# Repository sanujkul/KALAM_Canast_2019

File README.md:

# KALAM_Canast_2019    
These codes/files were written/developed for the Cansat competition 2019, USA.    

This folder have two types of files:  
1. Codes (.c, .c++, .ino)    
2. PCB designs    
  
Cansat 2019 was divided ino two parts: A payload and a container. Cansat is launched to the height of 750m and at the height of 450m, during descent journey,container would release the payload which will descent via auto-gyro mechanism.    
Cansat has to perform telemetry throughout its journey.   
  
Files descriptions:  
a. TeensyPayloadCodes : Have the Cansat's payload codes.   
b. Container_Final : Have the Cansat's container codes.    
c. Camera Stabilization Codes: Payload was divided into 2 subparts, minor subpart was camra stabilization system and these are codes for stabilizing the camera to shoot in a particular direction.   
d. Camera_Stabilisation_Tests: Codes written for testing Camera stabilization system.  
e. Bluetooth Tests: Camera stabilization setup used to communicate to main microcontroller (Teensy) via bluetooth and these are test codes for that.   
f. SumiranPCB: Contains PCB designs (Eagle Cad files) for the cansat.  
g. Packets: This is a class developed to use telemetry packet as an object to ease or work in organising the codeflow.

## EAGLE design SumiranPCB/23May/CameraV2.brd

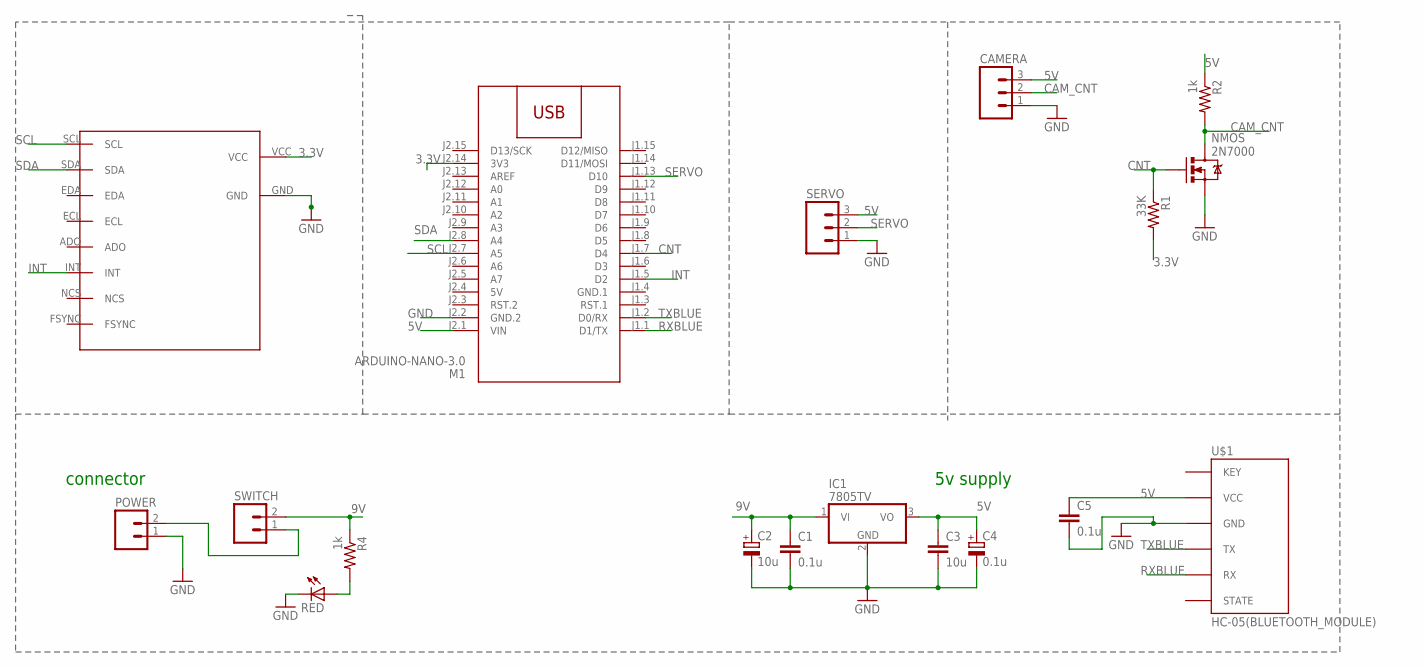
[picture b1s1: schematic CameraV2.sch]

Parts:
C1, C5: 0.1u; C025-025X050
C2: 10u; E2,5-6
C3: 10u; C025-025X050
C4: 0.1u; E2,5-6
CAMERA: CON-AMP-QUICK_M03; CON-AMP-QUICK_03P
IC1: 7805TV; TO220V
M1: ARDUINO-NANO-3.0
POWER: CEDT_JANUARY_2015_V5_M02; CEDT_JANUARY_2015_V5_02P
Q1: SPARKFUN-DISCRETESEMI_MOSFET-NCHANNEL2N7000; SPARKFUN-DISCRETESEMI_TO-92
R1: 33K; 0204/7
R2, R4: 1k; 0204/7
RED: red; LED3MM
SERVO: CON-AMP-QUICK_M03; CON-AMP-QUICK_03P
SWITCH: M02; 02P
U$1: HC-05(BLUETOOTH_MODULE); HC-05
U$2: MPU9250

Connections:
3.3V: M1.J2.14 (3V3), R1.2, U$2.VCC
5V: C3.1, C4.+, C5.1, CAMERA.3, IC1.3 (VO), M1.J2.1 (VIN), M1.J2.4 (5V), R2.1, SERVO.3, U$1.VCC
9V: C1.1, C2.+, IC1.1 (VI), R4.1, SWITCH.2
CAM_CNT: CAMERA.2, Q1.3 (D), R2.2
CNT: M1.J1.7 (D4), Q1.2 (G), R1.1
GND: C1.2, C2.-, C3.2, C4.-, C5.2, CAMERA.1, IC1.2 (GND), M1.J2.2 (GND.2), POWER.1, Q1.1 (S), RED.K (C), SERVO.1, U$1.GND, U$2.GND
GND.1: M1.J1.4 (GND.1)
INT: M1.J1.5 (D2), U$2.INT
unnamed: POWER.2, SWITCH.1
unnamed: R4.2, RED.A
RXBLUE: M1.J1.1 (D1/TX), U$1.RX
SCL: M1.J2.7 (A5), U$2.SCL
SDA: M1.J2.8 (A4), U$2.SDA
SERVO: M1.J1.13 (D10), SERVO.2
TXBLUE: M1.J1.2 (D0/RX), U$1.TX

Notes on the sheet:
connector
5v supply

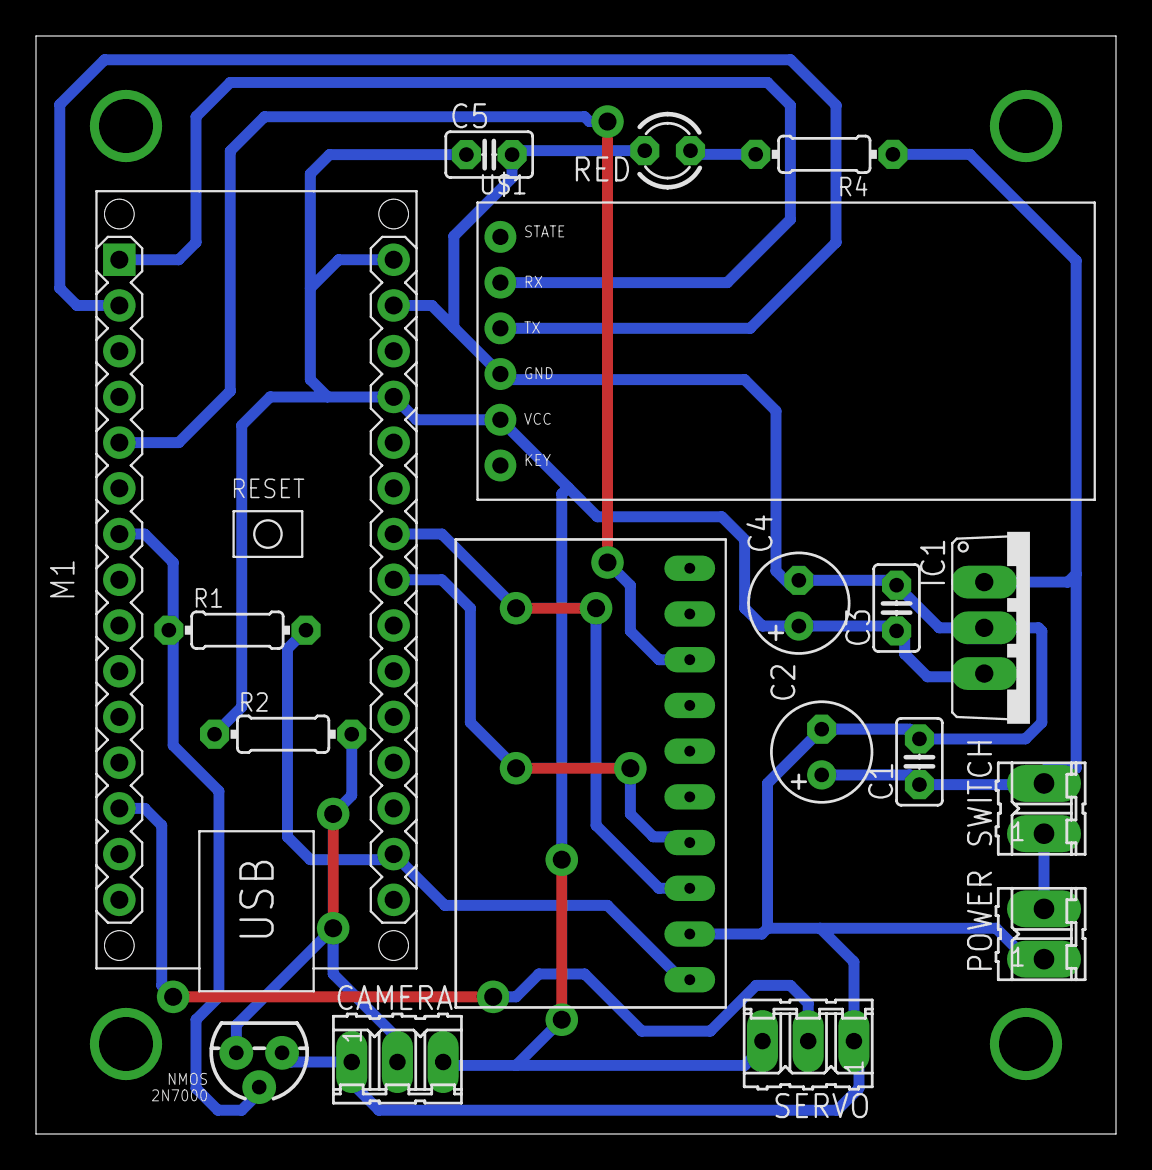
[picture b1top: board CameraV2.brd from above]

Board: 2 copper layers, 60.0 x 61.0 mm, 18 parts (0 on the bottom side), 14 nets.

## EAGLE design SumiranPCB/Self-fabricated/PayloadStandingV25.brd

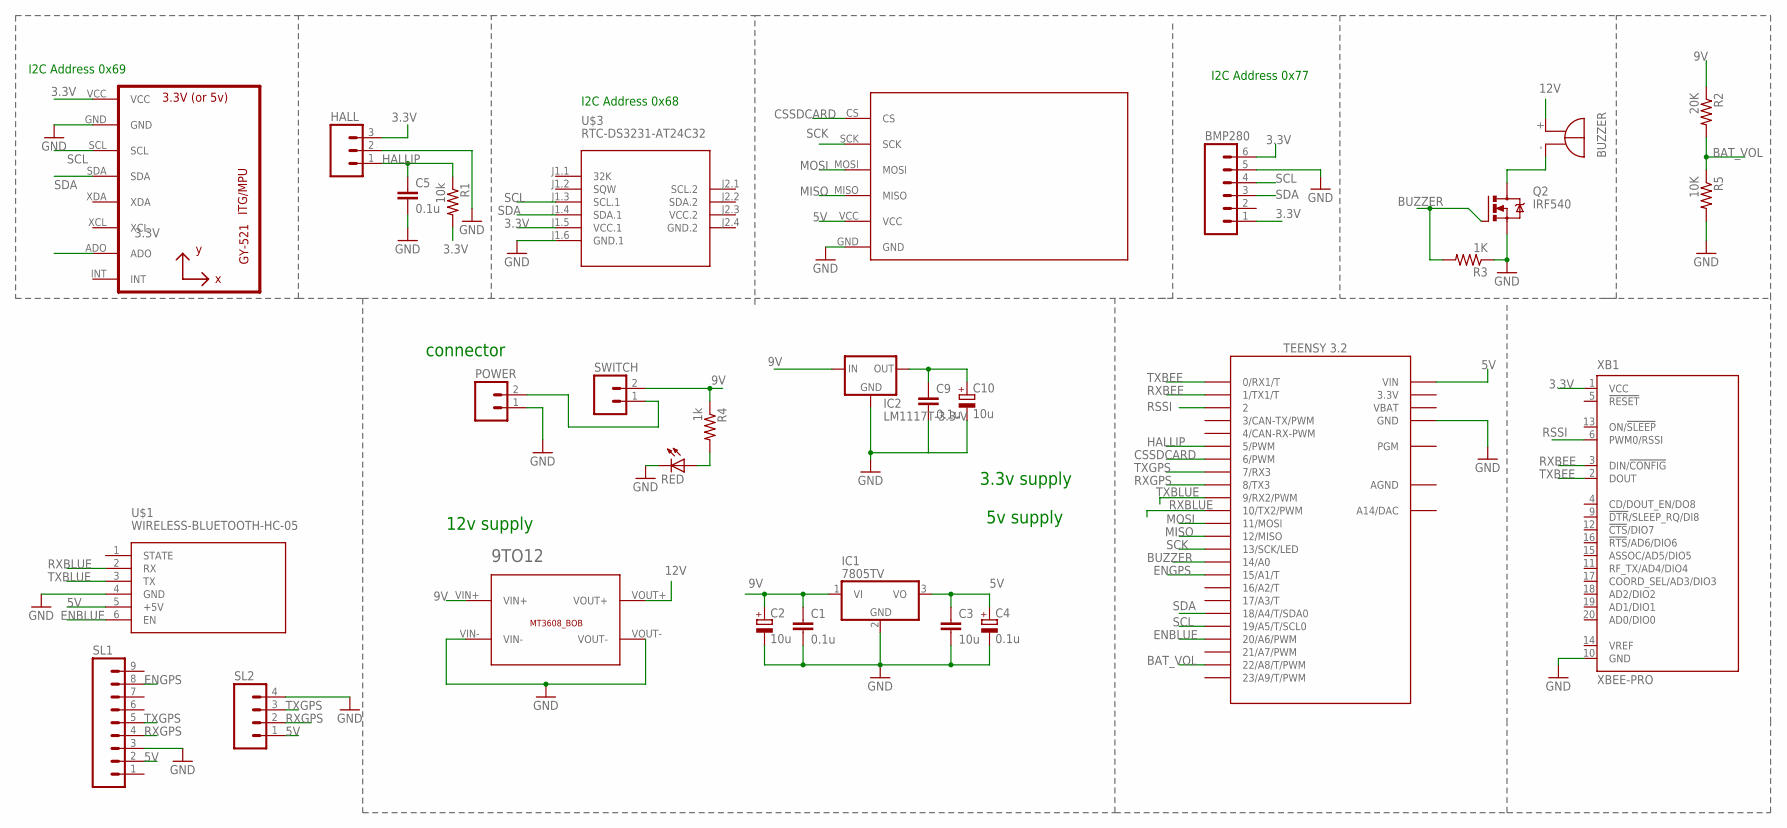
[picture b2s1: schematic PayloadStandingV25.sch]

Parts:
9TO12: BREAKOUTS_MT3608_BOB
BMP280: M06; 06P
C1, C5, C9: 0.1u; C025-025X050
C2, C10: 10u; E2,5-6
C3: 10u; C025-025X050
C4: 0.1u; E2,5-6
HALL: M03; 03P
IC1: 7805TV; TO220V
IC2: LM1117T-3.3-V; TO220V
POWER: CEDT_JANUARY_2015_V5_M02; CEDT_JANUARY_2015_V5_02P
Q2: IRF540; TO220BV
R1: 10k; 0204/7
R2: 20K; 0204/7
R3: 1K; 0204/7
R4: 1k; 0204/7
R5: 10K; 0204/7
RED: red; LED3MM
SG1: BUZZER_EB2209A
SL1: M09; 09P
SL2: CON-AMP-QUICK_M04; CON-AMP-QUICK_04P
SWITCH: M02; 02P
U1: GY-521MPU6050; GY-521
U$1: WIRELESS-BLUETOOTH-HC-05
U$2: TEENSY_3.1-3.2_OUTER_ROW; TEENSY_3.0-3.2&LC_OUTER_ROW
U$3: RTC-DS3231-AT24C32
U$5: SDCARD; M0SDCARDMODULE
XB1: XBEE-PRO

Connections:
3.3V: BMP280.1, BMP280.6, C9.1, C10.+, HALL.3, IC2.2 (OUT), R1.2, U1.ADO, U1.VCC, U$2.3.3V, U$2.3.3V1 (3.3V), U$3.J1.5 (VCC.1), XB1.1 (VCC)
5V: C3.1, C4.+, IC1.3 (VO), SL1.2, SL2.1, U$1.5 (+5V), U$2.VIN, U$5.VCC
9V: 9TO12.VIN+, C1.1, C2.+, IC1.1 (VI), IC2.3 (IN), R2.1, R4.1, SWITCH.2
12V: 9TO12.VOUT+, SG1.+
AGND: U$2.AGND
BAT_VOL: R2.2, R5.1, U$2.22/A8 (22/A8/T/PWM)
BUZZER: Q2.G, R3.2, U$2.14/A0
CSSDCARD: U$2.6 (6/PWM), U$5.CS
ENBLUE: U$1.6 (EN), U$2.20/A6 (20/A6/PWM)
ENGPS: SL1.8, U$2.15/A1 (15/A1/T)
GND: 9TO12.VIN-, 9TO12.VOUT-, BMP280.5, C1.2, C2.-, C3.2, C4.-, C5.2, C9.2, C10.-, HALL.2, IC1.2 (GND), IC2.1 (GND), POWER.1, Q2.S, R3.1, R5.2, RED.K (C), SL1.3, SL2.4, U1.GND, U$1.4 (GND), U$2.GND, U$2.GND1 (GND), U$3.J1.6 (GND.1), U$5.GND, XB1.10 (GND)
GND.2: U$3.J2.4 (GND.2)
HALLIP: C5.1, HALL.1, R1.1, U$2.5 (5/PWM)
MISO: U$2.12 (12/MISO), U$5.MISO
MOSI: U$2.11 (11/MOSI), U$5.MOSI
unnamed: POWER.2, SWITCH.1
unnamed: R4.2, RED.A
unnamed: Q2.D, SG1.-
RSSI: U$2.2, XB1.6 (PWM0/RSSI)
RXBEE: U$2.1 (1/TX1/T), XB1.3 (DIN/!CONFIG)
RXBLUE: U$1.2 (RX), U$2.10 (10/TX2/PWM)
RXGPS: SL1.4, SL2.2, U$2.8 (8/TX3)
SCK: U$2.13 (13/SCK/LED), U$5.SCK
SCL: BMP280.4, U1.SCL, U$2.19/A5 (19/A5/T/SCL0), U$3.J1.3 (SCL.1)
SDA: BMP280.3, U1.SDA, U$2.18/A4 (18/A4/T/SDA0), U$3.J1.4 (SDA.1)
TXBEE: U$2.0 (0/RX1/T), XB1.2 (DOUT)
TXBLUE: U$1.3 (TX), U$2.9 (9/RX2/PWM)
TXGPS: SL1.5, SL2.3, U$2.7 (7/RX3)
VBAT: U$2.VBAT
VCC.2: U$3.J2.3 (VCC.2)

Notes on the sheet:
connector
3.3v supply
5v supply
12v supply
I2C Address 0x77
I2C Address 0x68
I2C Address 0x69

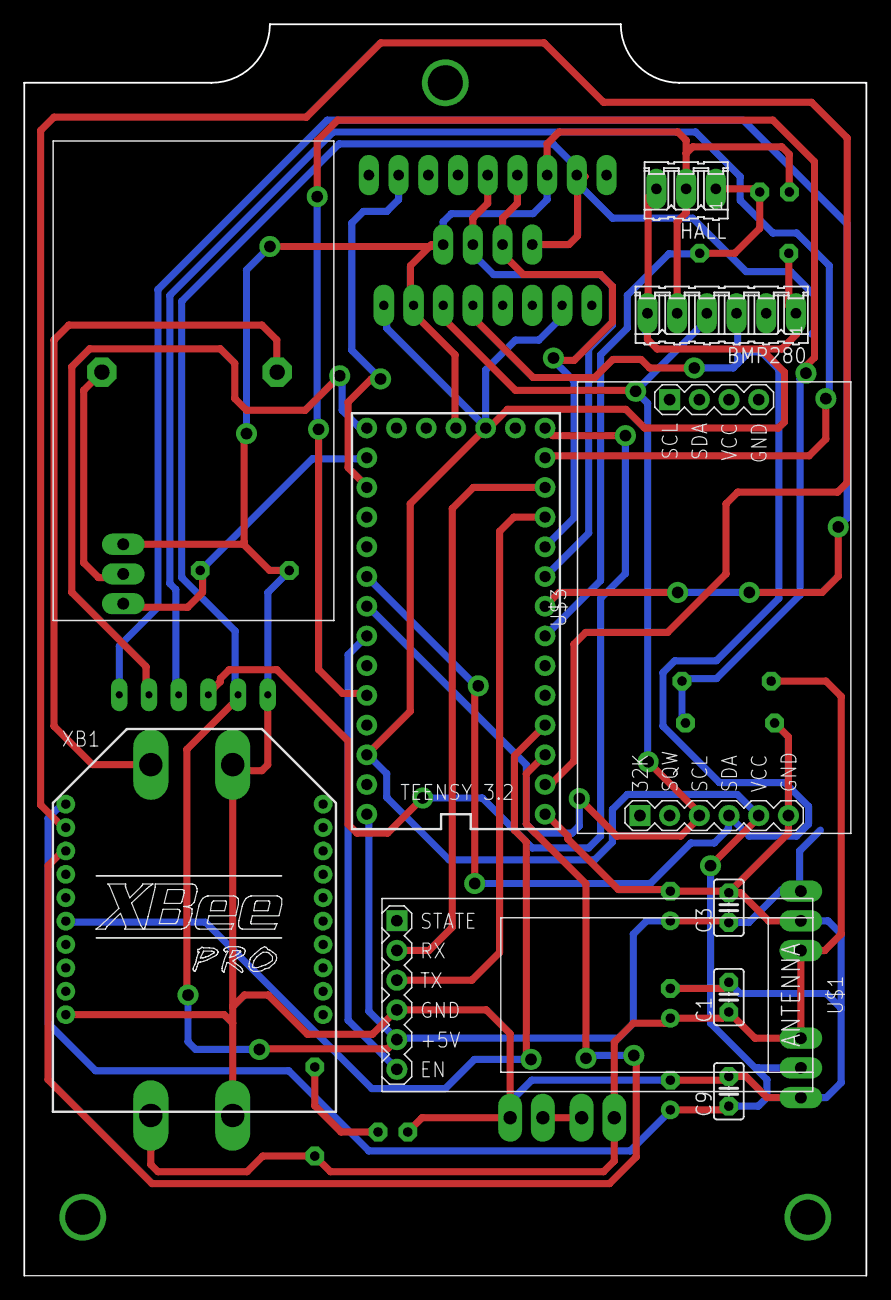
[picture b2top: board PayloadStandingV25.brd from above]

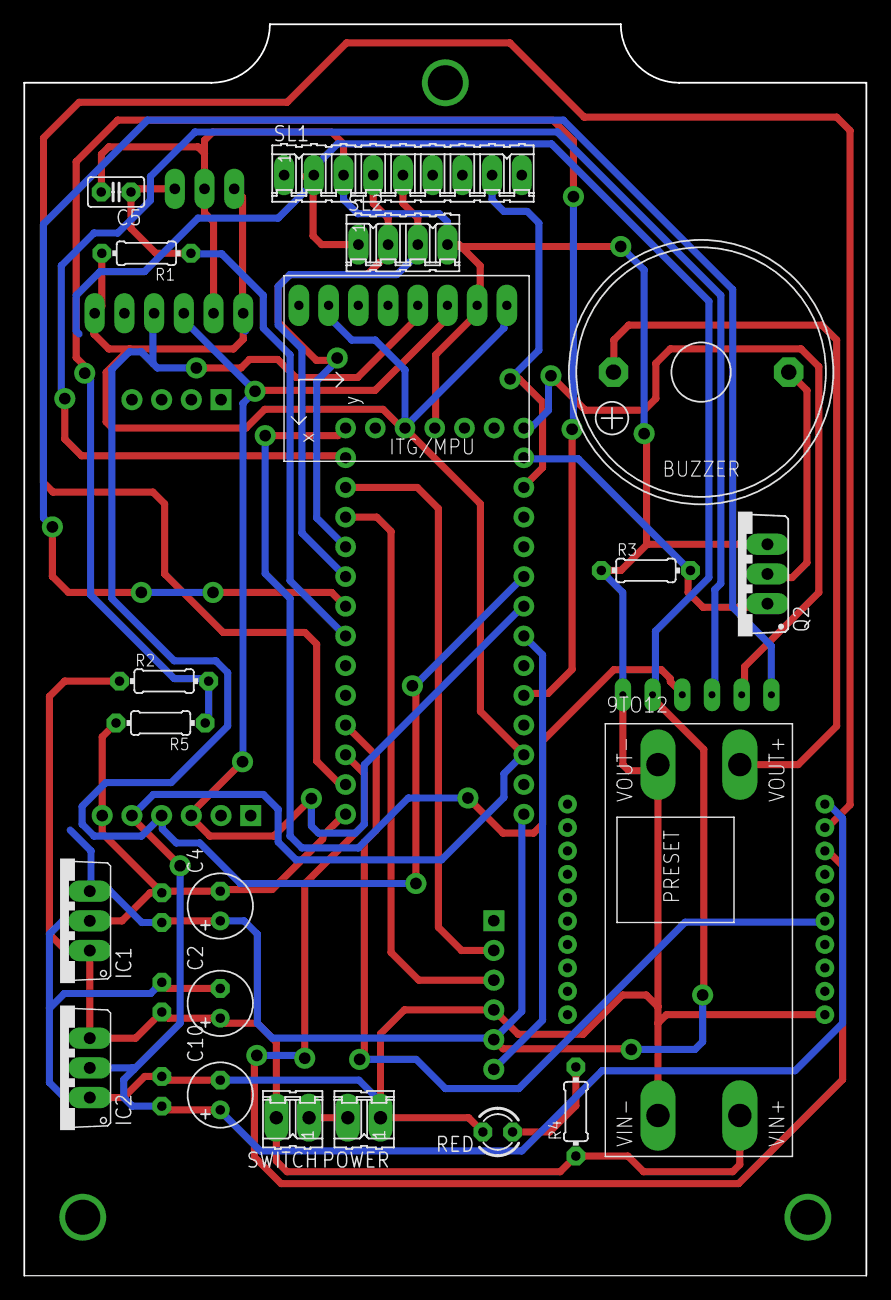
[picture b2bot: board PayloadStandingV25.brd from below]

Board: 2 copper layers, 72.0 x 107.0 mm, 30 parts (20 on the bottom side), 26 nets.

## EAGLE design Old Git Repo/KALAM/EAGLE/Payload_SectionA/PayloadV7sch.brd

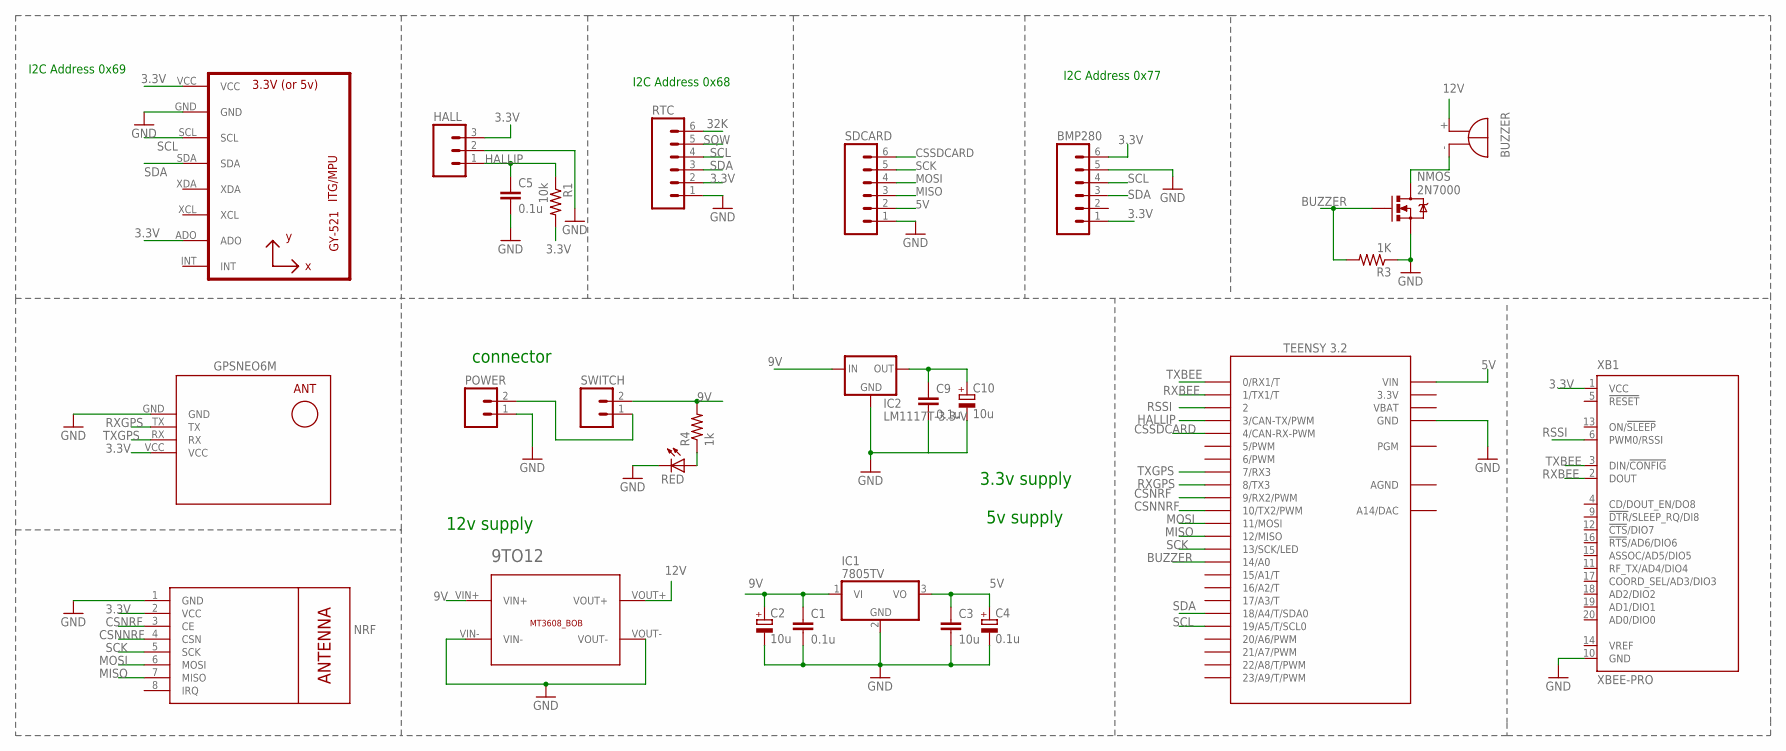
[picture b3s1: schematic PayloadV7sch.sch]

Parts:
9TO12: BREAKOUTS_MT3608_BOB
BMP280: M06; 06P
C1, C5, C9: 0.1u; C025-025X050
C2, C10: 10u; E2,5-6
C3: 10u; C025-025X050
C4: 0.1u; E2,5-6
HALL: M03; 03P
IC1: 7805TV; TO220V
IC2: LM1117T-3.3-V; TO220V
M1: WIRELESS-NRF24L01
POWER: CEDT_JANUARY_2015_V5_M02; CEDT_JANUARY_2015_V5_02P
Q1: SPARKFUN-DISCRETESEMI_MOSFET-NCHANNEL2N7000; SPARKFUN-DISCRETESEMI_TO-92
R1: 10k; 0204/7
R3: 1K; 0204/7
R4: 1k; 0204/7
RED: red; LED3MM
RTC: M06; 06P
SDCARD: M06; 06P
SG1: BUZZER_EB2209A
SWITCH: CEDT_JANUARY_2015_V5_M02; CEDT_JANUARY_2015_V5_02P
U1: GY-521MPU6050; GY-521
U$2: TEENSY_3.1-3.2_OUTER_ROW; TEENSY_3.0-3.2&LC_OUTER_ROW
U$3: GPS-RECEIVER-NEO6M
XB1: XBEE-PRO

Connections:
3.3V: BMP280.1, BMP280.6, C9.1, C10.+, HALL.3, IC2.2 (OUT), M1.2 (VCC), R1.2, RTC.2, U1.ADO, U1.VCC, U$2.3.3V, U$2.3.3V1 (3.3V), U$3.VCC, XB1.1 (VCC)
5V: C3.1, C4.+, IC1.3 (VO), SDCARD.2, U$2.VIN
9V: 9TO12.VIN+, C1.1, C2.+, IC1.1 (VI), IC2.3 (IN), R4.2
12V: 9TO12.VOUT+, SG1.+
32K: RTC.6
AGND: U$2.AGND
BUZZER: Q1.2 (G), R3.2, U$2.14/A0
CSNNRF: M1.4 (CSN), U$2.10 (10/TX2/PWM)
CSNRF: M1.3 (CE), U$2.9 (9/RX2/PWM)
CSSDCARD: SDCARD.6, U$2.4 (4/CAN-RX-PWM)
GND: 9TO12.VIN-, 9TO12.VOUT-, BMP280.5, C1.2, C2.-, C3.2, C4.-, C5.2, C9.2, C10.-, HALL.2, IC1.2 (GND), IC2.1 (GND), M1.1 (GND), POWER.1, Q1.1 (S), R3.1, RED.K (C), RTC.1, SDCARD.1, U1.GND, U$2.GND, U$2.GND1 (GND), U$3.GND, XB1.10 (GND)
HALLIP: C5.1, HALL.1, R1.1, U$2.3 (3/CAN-TX/PWM)
MISO: M1.7 (MISO), SDCARD.3, U$2.12 (12/MISO)
MOSI: M1.6 (MOSI), SDCARD.4, U$2.11 (11/MOSI)
unnamed: R4.1, RED.A
unnamed: Q1.3 (D), SG1.-
RSSI: U$2.2, XB1.6 (PWM0/RSSI)
RXBEE: U$2.1 (1/TX1/T), XB1.2 (DOUT)
RXGPS: U$2.8 (8/TX3), U$3.TX
SCK: M1.5 (SCK), SDCARD.5, U$2.13 (13/SCK/LED)
SCL: BMP280.4, RTC.4, U1.SCL, U$2.19/A5 (19/A5/T/SCL0)
SDA: BMP280.3, RTC.3, U1.SDA, U$2.18/A4 (18/A4/T/SDA0)
SQW: RTC.5
TXBEE: U$2.0 (0/RX1/T), XB1.3 (DIN/!CONFIG)
TXGPS: U$2.7 (7/RX3), U$3.RX
VBAT: U$2.VBAT

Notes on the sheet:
connector
3.3v supply
5v supply
12v supply
I2C Address 0x77
I2C Address 0x68
I2C Address 0x69

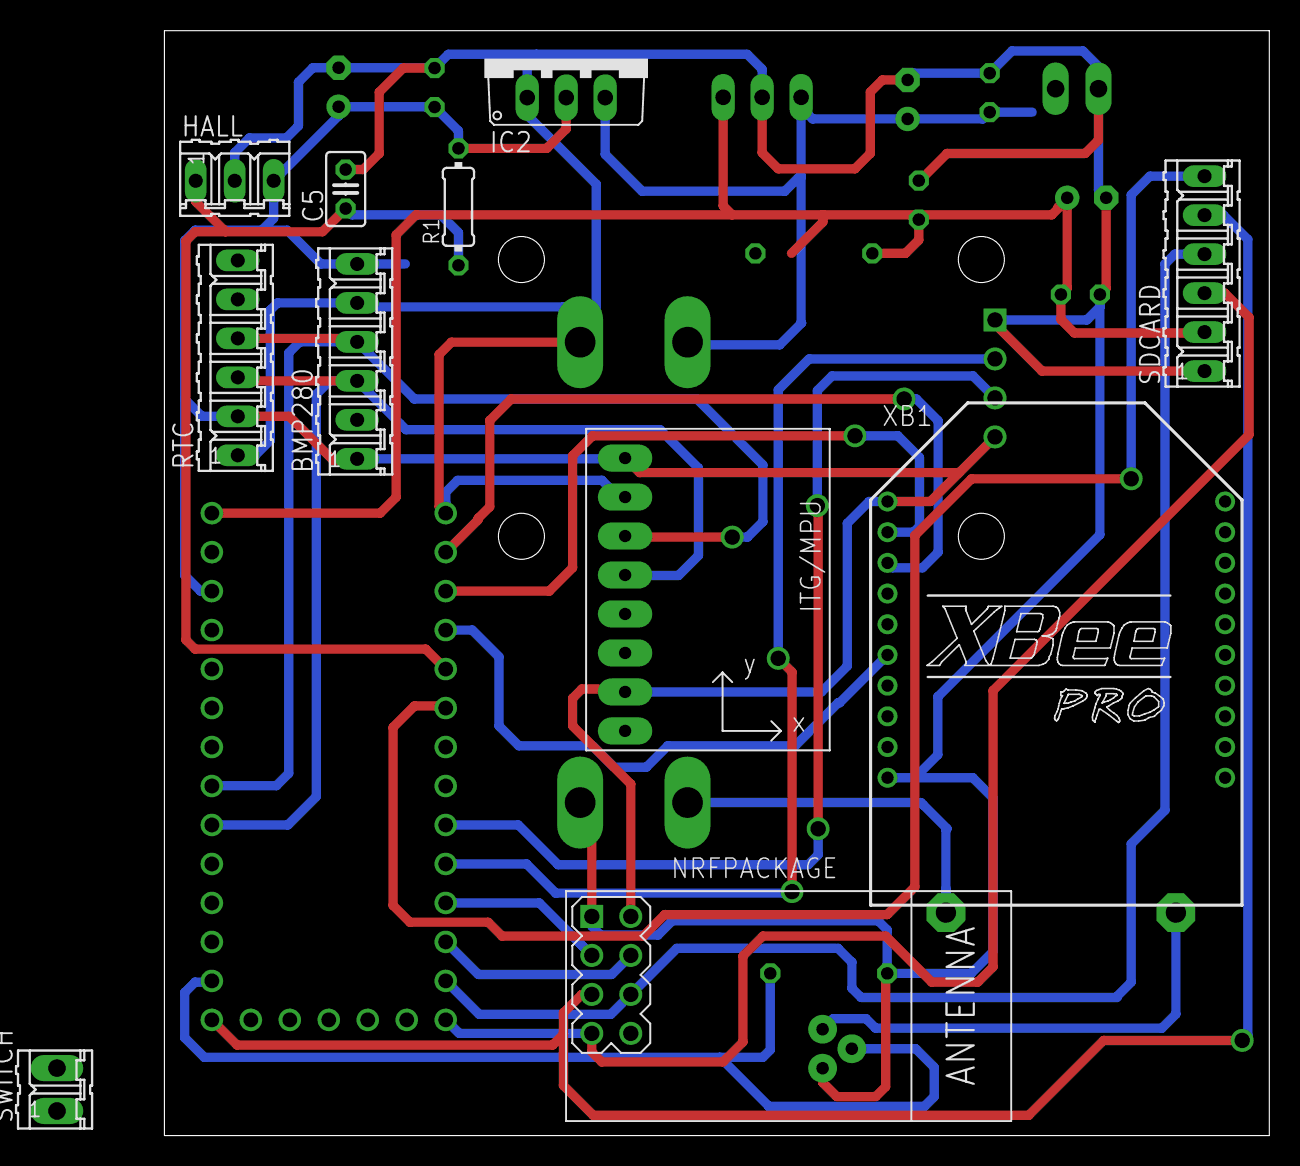
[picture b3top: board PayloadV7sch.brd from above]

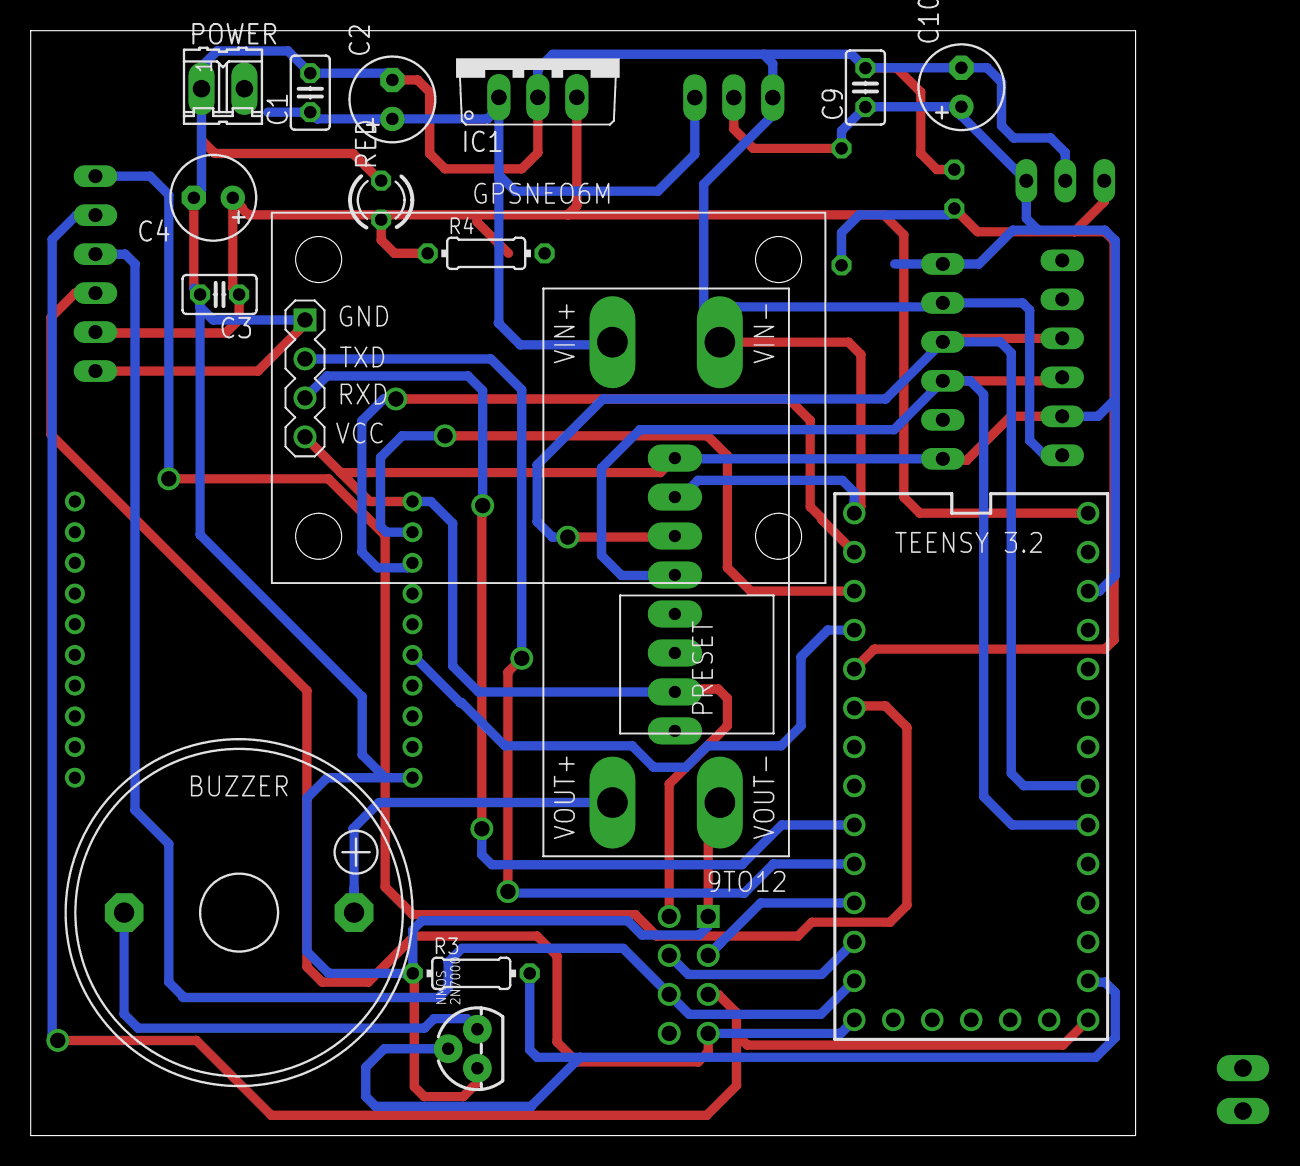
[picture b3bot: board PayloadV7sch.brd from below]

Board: 2 copper layers, 72.0 x 72.0 mm, 27 parts (16 on the bottom side), 22 nets.

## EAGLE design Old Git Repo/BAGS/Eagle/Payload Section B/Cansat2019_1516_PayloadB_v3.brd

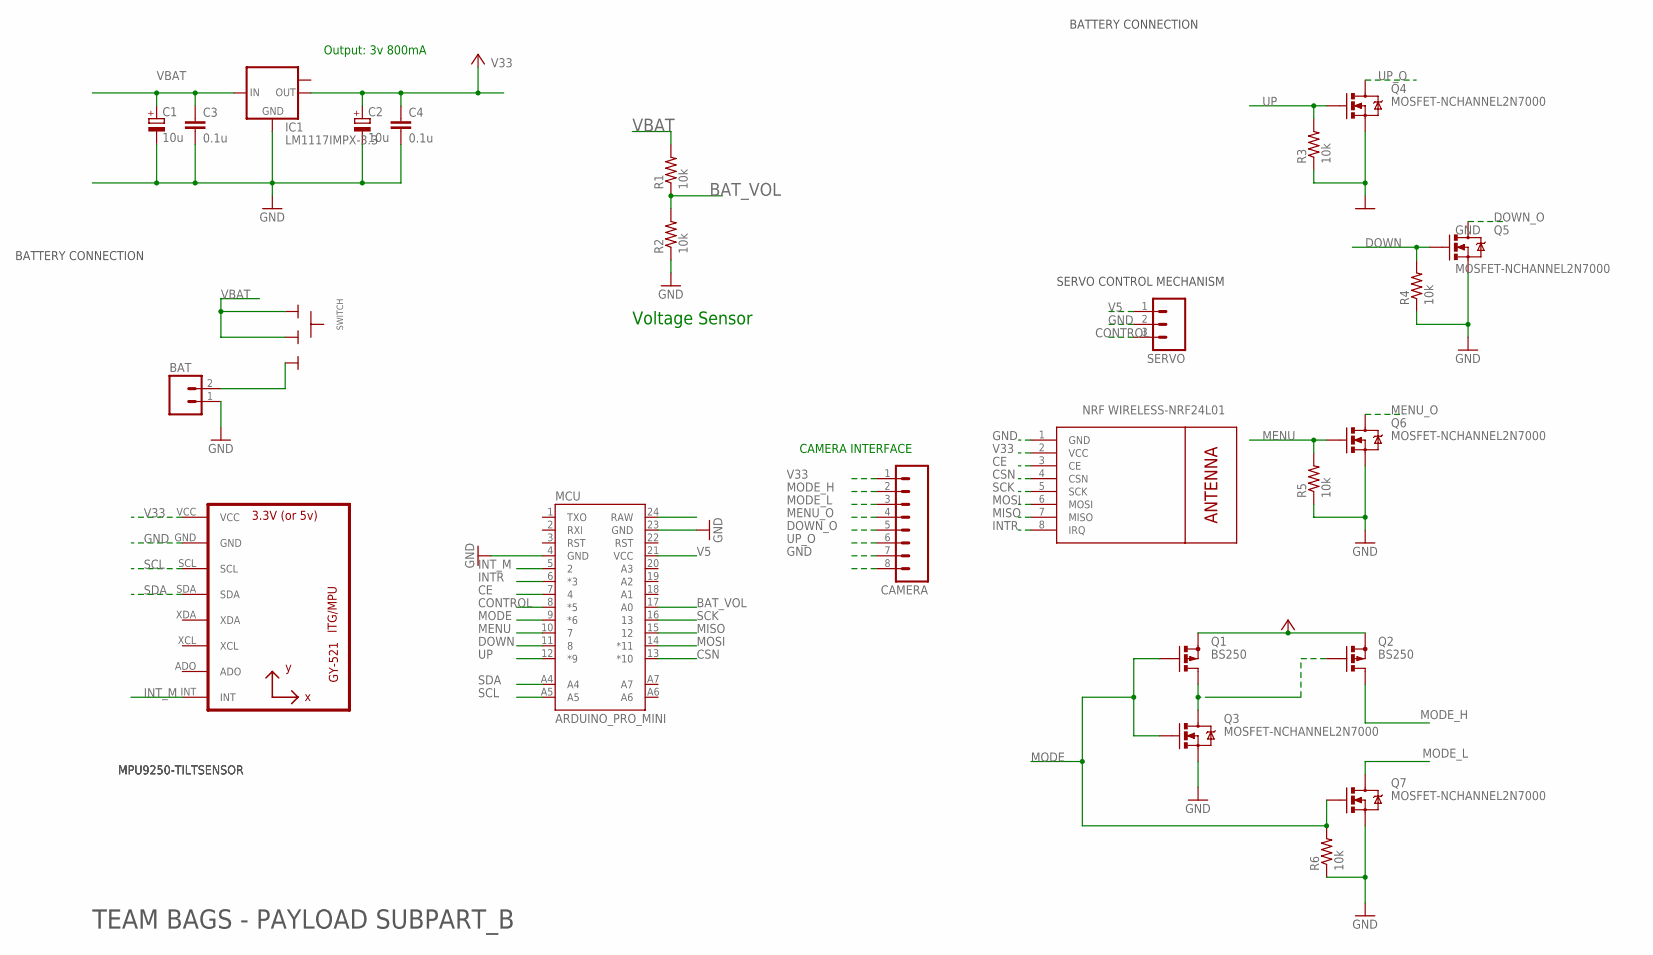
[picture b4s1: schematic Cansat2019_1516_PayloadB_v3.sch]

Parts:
BAT: M02; 02P
C1, C2: 10u; CT3528
C3, C4: 0.1u; C0805
CAMERA: M08; 08P
IC1: LM1117IMPX-3.3; SOT223
MCU: ARDUINO_PRO_MINI
MPU: GY-521MPU6050; GY-521
NRF: WIRELESS-NRF24L01
Q1, Q2: BS250; SOT54E
Q3, Q4, Q5, Q6, Q7: MOSFET-NCHANNEL2N7000; TO-92
R1, R2, R3, R4, R5, R6: 10k; R0805
SERVO: M03; 03P
SWITCH: SLIDESWITCH-BIG; BIGSWITCH

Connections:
BAT_VOL: MCU.17 (A0), R1.1, R2.2
CE: MCU.7 (4), NRF.3 (CE)
CONTROL: MCU.8 (*5), SERVO.3
CSN: MCU.13 (*10), NRF.4 (CSN)
DOWN: MCU.11 (8), Q5.2 (G), R4.2
DOWN_O: CAMERA.5, Q5.3 (D)
GND: BAT.1, C1.-, C2.-, C3.2, C4.2, CAMERA.7, IC1.1 (GND), MCU.4 (GND), MCU.23 (GND), MPU.GND, NRF.1 (GND), Q3.1 (S), Q4.1 (S), Q5.1 (S), Q6.1 (S), Q7.1 (S), R2.1, R3.1, R4.1, R5.1, R6.1, SERVO.2
INTR: MCU.6 (*3), NRF.8 (IRQ)
INT_M: MCU.5 (2), MPU.INT
MENU: MCU.10 (7), Q6.2 (G), R5.2
MENU_O: CAMERA.4, Q6.3 (D)
MISO: MCU.15 (12), NRF.7 (MISO)
MODE: MCU.9 (*6), Q1.G, Q3.2 (G), Q7.2 (G), R6.2
MODE_H: CAMERA.2, Q2.D
MODE_L: CAMERA.3, Q7.3 (D)
MOSI: MCU.14 (*11), NRF.6 (MOSI)
unnamed: BAT.2, SWITCH.3
unnamed: Q1.D, Q2.G, Q3.3 (D)
SCK: MCU.16 (13), NRF.5 (SCK)
SCL: MCU.A5, MPU.SCL
SDA: MCU.A4, MPU.SDA
UP: MCU.12 (*9), Q4.2 (G), R3.2
UP_O: CAMERA.6, Q4.3 (D)
V5: MCU.21 (VCC), SERVO.1
V33: C2.+, C4.1, CAMERA.1, IC1.2 (OUT), MPU.VCC, NRF.2 (VCC)
VBAT: C1.+, C3.1, IC1.3 (IN), R1.2, SWITCH.1, SWITCH.2
VCC: Q1.S, Q2.S

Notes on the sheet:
Output: 3v 800mA
MPU9250-TILTSENSOR
BATTERY CONNECTION
SERVO CONTROL MECHANISM
CAMERA INTERFACE
TEAM BAGS - PAYLOAD SUBPART_B
Voltage Sensor

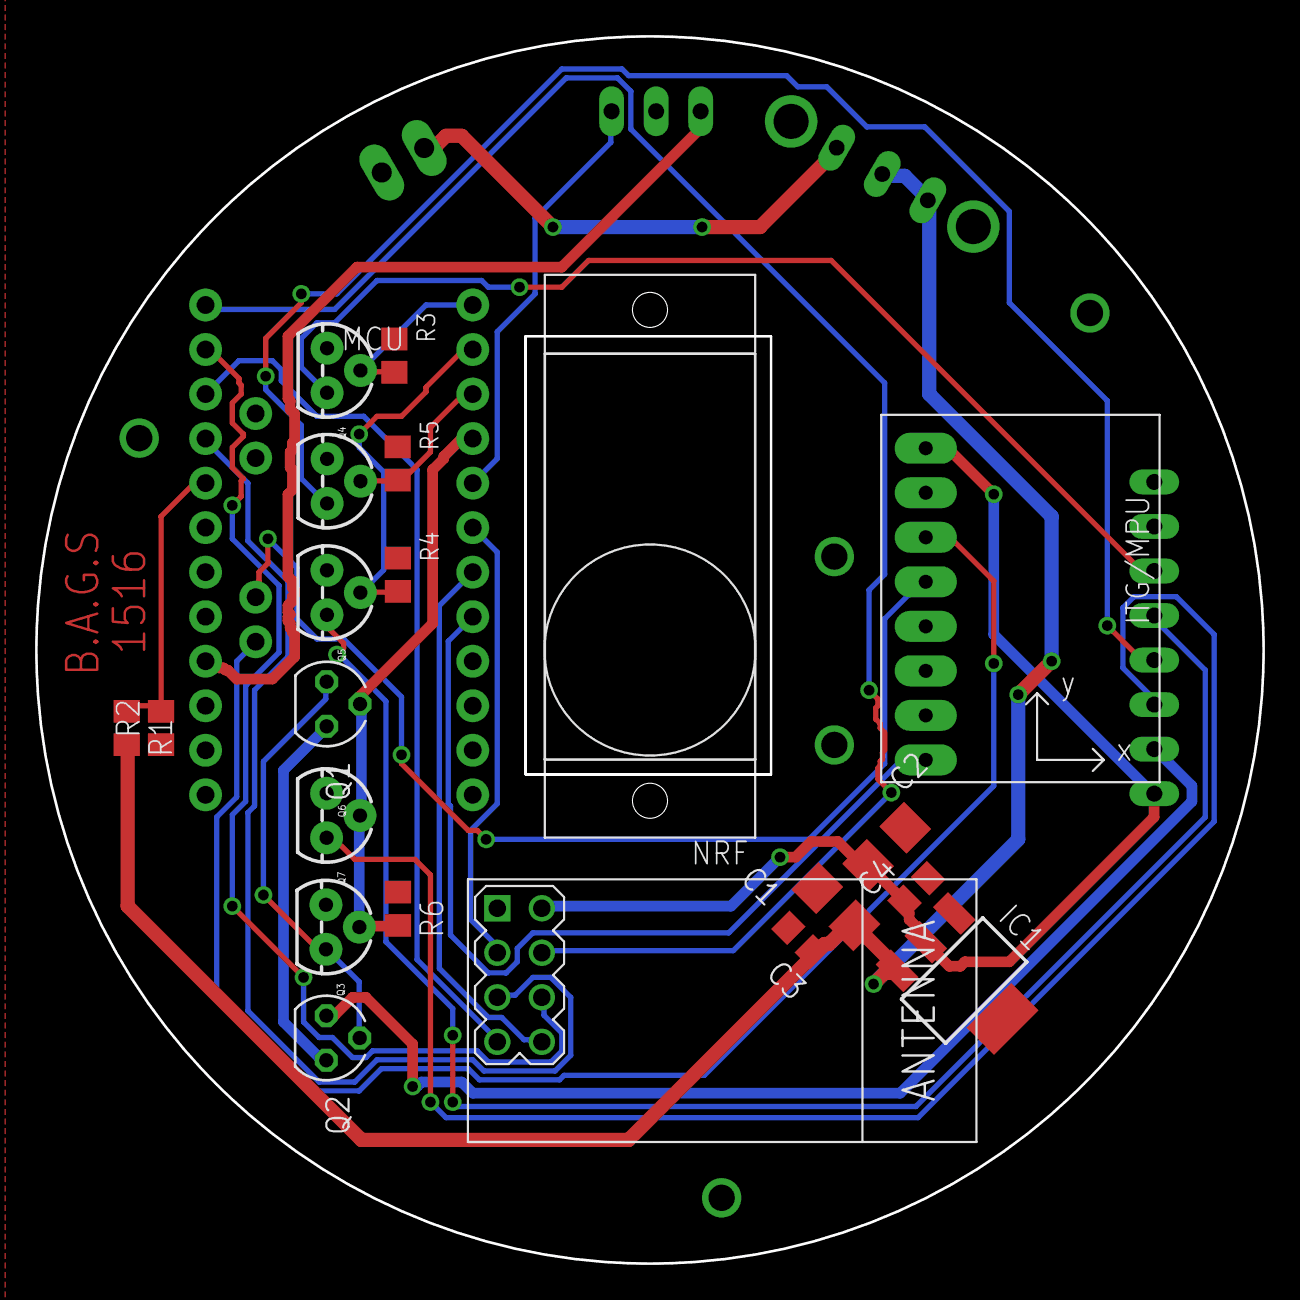
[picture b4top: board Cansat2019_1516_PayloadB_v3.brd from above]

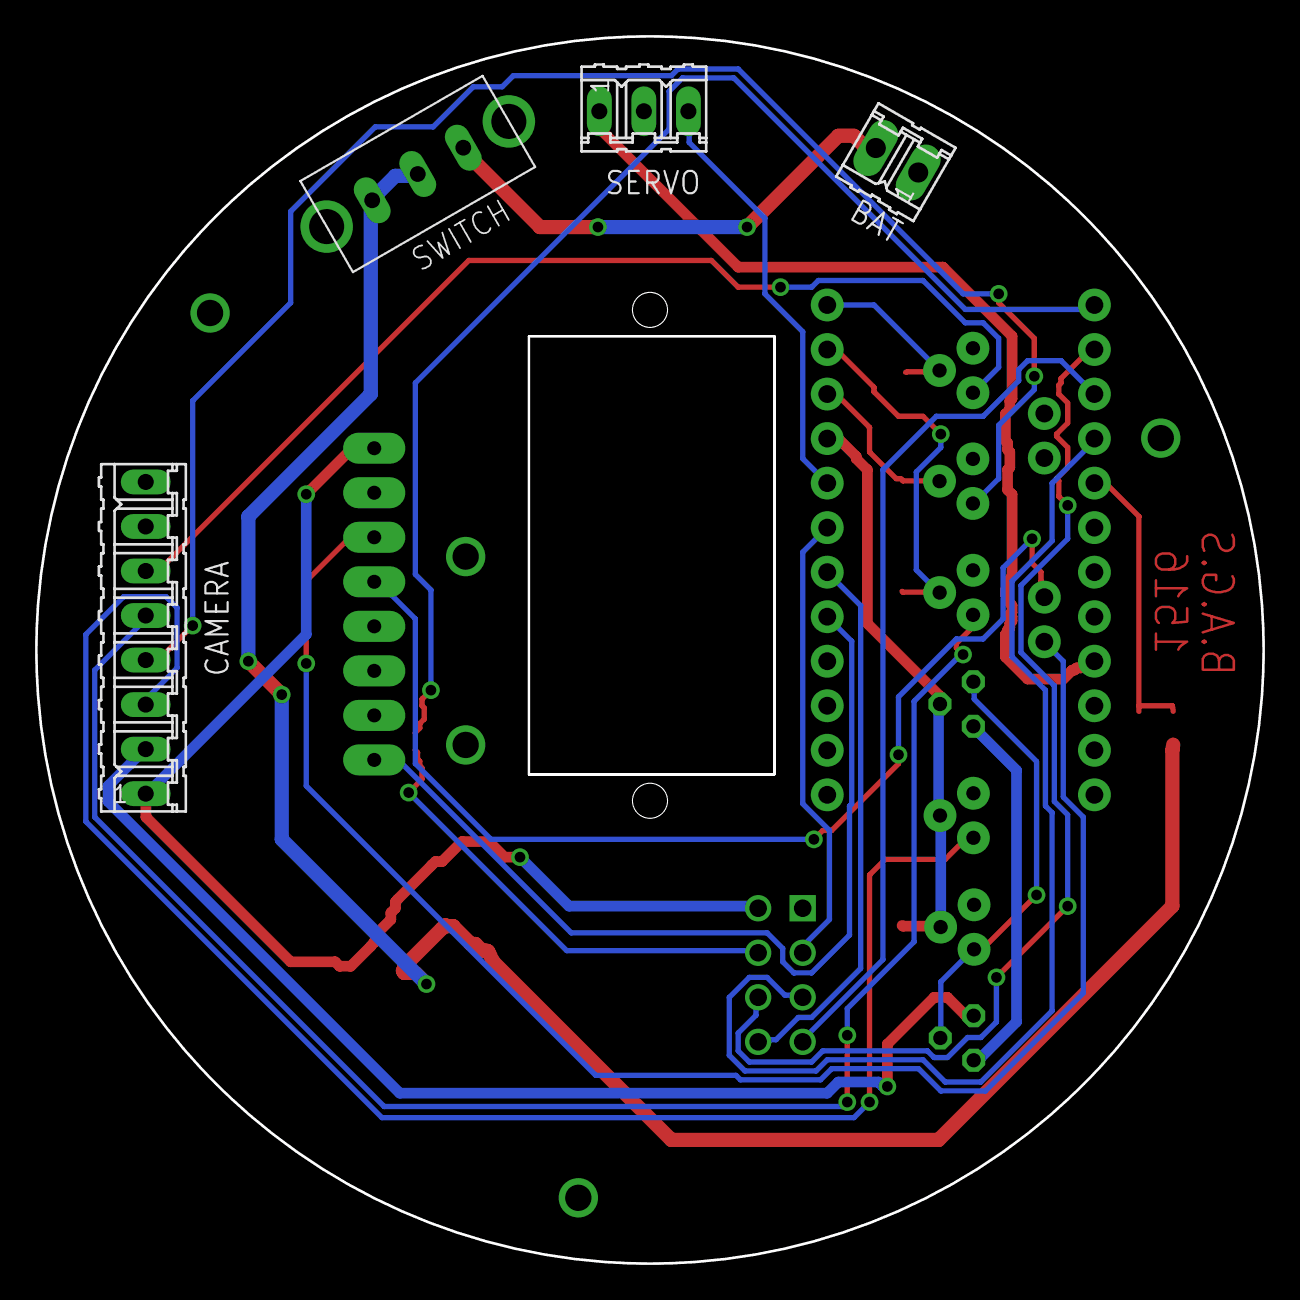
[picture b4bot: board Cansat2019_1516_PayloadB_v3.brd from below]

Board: 2 copper layers, 70.0 x 70.0 mm, 26 parts (4 on the bottom side), 27 nets.

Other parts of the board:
U$1: SG90_TOP

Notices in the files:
parts and their libraries:
SparkFun-Connectors: Licensing: Creative Commons ShareAlike 4.0 International - https://creativecommons.org/licenses/by-sa/4.0
diy-modules: Released under the Creative Commons Attribution 4.0 International License: http://creativecommons.org/licenses/by/4.0
